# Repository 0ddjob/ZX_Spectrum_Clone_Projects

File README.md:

# ZX Spectrum Clone Projects
Hardware projects & information for Sinclair ZX Spectrum clone computers

## [Datasheets](/Datasheets)
Relevant datasheets for PCB designs.<br>

## [Belarus Byte DIN to VGA](/Belarus_Byte_DIN-to-VGA)
Convert 5-pin DIN video output to DE15 VGA:

- Pin 1 = synch
- Pin 2 = ground
- Pin 3 = blue
- Pin 4 = green
- Pin 5 = red

## [Leningrad-2 DIN to VGA](/Leningrad_2_DIN-to-VGA)
Convert 5-pin DIN video output to DE15 VGA:

- Pin 1 = audio
- Pin 2 = blue
- Pin 3 = red
- Pin 4 = video
- Pin 5 = green
- Sheath = ground

## [Leningrad 2 Expansion](/Leningrad_2_Expansion)
Experimental board to convert the 2x32 (2.5mm pin pitch) expansion header to standard ZX Spectrum edge connector.

## [Moldova BYTE DIN to VGA](/Moldova_BYTE_DIN-to-VGA)
There are two types of BYTE from Moldova: the "Red BYTE" (in a red case with 7-pin DIN) and the "Speccy BYTE" (looks like a Spectrum with a 5-pin DIN).

- Pin 1 = composite video (not connected)
- Pin 2 = composite synch
- Pin 3 = blue
- Pin 4 = green
- Pin 5 = red
- Pin 6 = ground
- Pin 7 = audio

## [Nafanya](/Nafanya)

## [Orel BK DIN to VGA](/Orel_BK_DIN-to-VGA)

## [RGB to VGA](/RGB_to_VGA)

## [Sirius](/Sirius)

## [ZX Spectrum Pioneer 2 Keyboard](/ZX_Spectrum_Pioneer-2_Keyboard)
Work in progress replacement.

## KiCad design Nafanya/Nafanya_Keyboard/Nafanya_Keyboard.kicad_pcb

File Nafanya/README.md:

# Нафаня (Nafanya) ZX Spectrum Clone
The Нафаня is a late Soviet-era (1991) ZX Spectrum clone out of the Russian SFSR.<br>  
My Нафаня is serial no. 00872.<br>

My particular example has a nice, ceramic Z80 from DDR (East Germany) as well as a ceramic БМК (Basic Matrix Crystal, Soviet version of a ULA or Gate Array).<br>

It looked like the original, good quality capacitors were removed from my machine due to their precious-metal content.  They were substituted with poor quality replacements.  I, in turn, replaced them with better quality ones ... this greatly stabilised the RGB video output!  I also added a lot more decoupling capacitors - there was provision for them on the board but they were not installed.<br>

## [Video](https://www.youtube.com/playlist?list=PL5pwokf56wMLiZ0rl97ZL9QdxtgF-uewT)
My YouTube videos:
- [Part 1 (Power On & Troubleshooting)](https://youtu.be/pPQIZv7UhS0)
- [Part 2 (Quick Update)](https://youtu.be/jH4AOVMjng8)
- [Part 3 (Replacement Keyboard Plans)](https://youtu.be/gZ2KwFe9IKs)

## [ROM](/ROM)
The ROM from my machine can be found in this repository.<br>

It has a pretty cool boot screen - I assume this is depicting the character "Нафаня" the computer is named after, a домовой (domovoy, or house spirit) from the Soviet animated film series "Домовёнок Кузя" (Domovyonok Kuzya, or "Kuzya the Little Domovoy") which is based on a children's book by Tatiana Aleksandrova.<br>

## [New Keyboard](/Nafanya_Keyboard)
The keyboard is not terribly good. Here is a re-designed one using tactile switches that should fit in the existing case.<br>

### Status
6-Apr-2025:  Still being finalised. The switch positions are slightly off as you go from left to right.
17-Apr-2025: Finalised switch layout, sent for test fabrication.

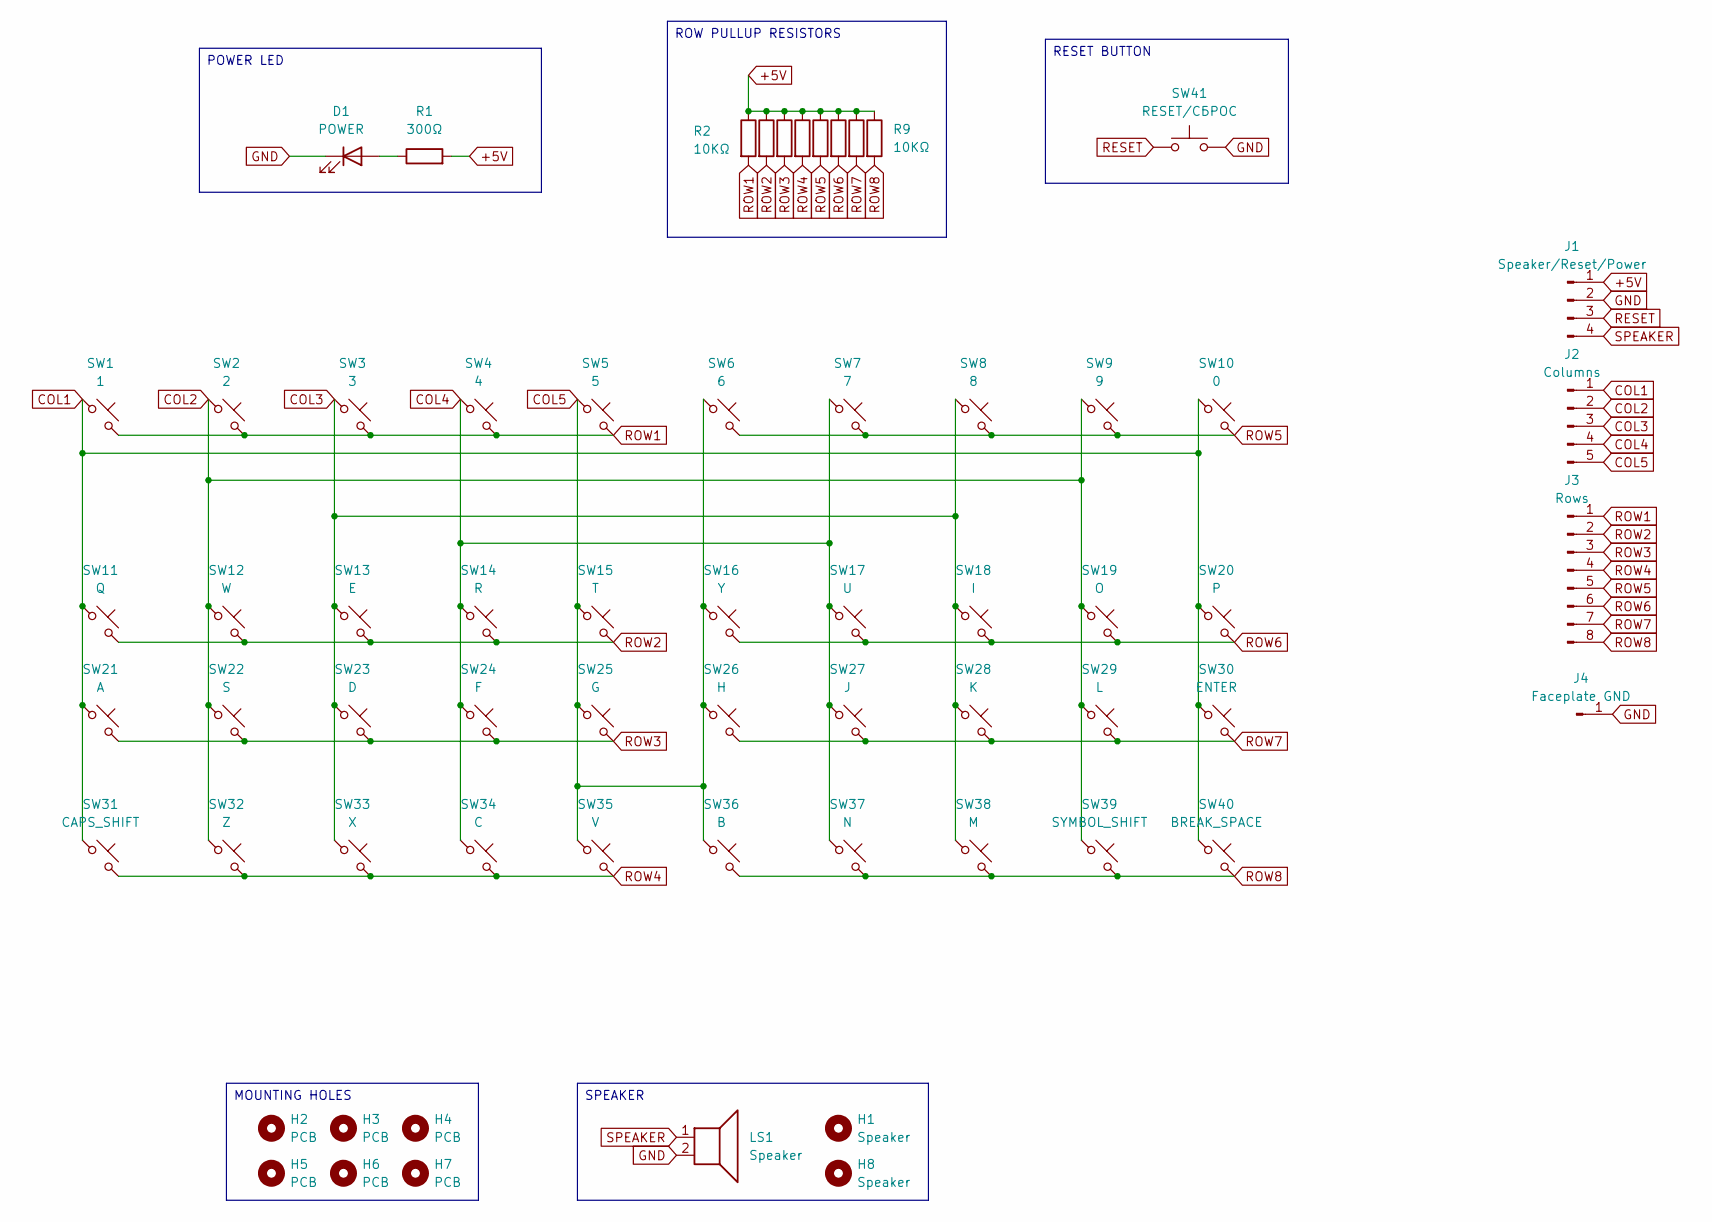
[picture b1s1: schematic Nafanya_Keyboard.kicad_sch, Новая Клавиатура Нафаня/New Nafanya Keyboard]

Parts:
D1: POWER; LED_D5.0mm
H1, H8: Speaker; MountingHole_3.2mm_M3
H2, H3, H4, H5, H6, H7: PCB; MountingHole_3.2mm_M3
J1: Speaker/Reset/Power; PinHeader_1x04_P2.54mm_Horizontal
J2: Columns; PinHeader_1x05_P2.54mm_Horizontal
J3: Rows; PinHeader_1x08_P2.54mm_Horizontal
J4: Faceplate GND; PinSocket_1x01_P2.54mm_Vertical
LS1: Speaker; PinHeader_1x02_P2.54mm_Vertical
R1: 300Ω; R_Axial_DIN0207_L6.3mm_D2.5mm_P7.62mm_Horizontal
R2, R3, R4, R5, R6, R7, R8, R9: 10KΩ; R_Axial_DIN0207_L6.3mm_D2.5mm_P7.62mm_Horizontal
SW1: 1; SW_PUSH_6mm
SW2: 2; SW_PUSH_6mm
SW3: 3; SW_PUSH_6mm
SW4: 4; SW_PUSH_6mm
SW5: 5; SW_PUSH_6mm
SW6: 6; SW_PUSH_6mm
SW7: 7; SW_PUSH_6mm
SW8: 8; SW_PUSH_6mm
SW9: 9; SW_PUSH_6mm
SW10: 0; SW_PUSH_6mm
SW11: Q; SW_PUSH_6mm
SW12: W; SW_PUSH_6mm
SW13: E; SW_PUSH_6mm
SW14: R; SW_PUSH_6mm
SW15: T; SW_PUSH_6mm
SW16: Y; SW_PUSH_6mm
SW17: U; SW_PUSH_6mm
SW18: I; SW_PUSH_6mm
SW19: O; SW_PUSH_6mm
SW20: P; SW_PUSH_6mm
SW21: A; SW_PUSH_6mm
SW22: S; SW_PUSH_6mm
SW23: D; SW_PUSH_6mm
SW24: F; SW_PUSH_6mm
SW25: G; SW_PUSH_6mm
SW26: H; SW_PUSH_6mm
SW27: J; SW_PUSH_6mm
SW28: K; SW_PUSH_6mm
SW29: L; SW_PUSH_6mm
SW30: ENTER; SW_PUSH_6mm
SW31: CAPS_SHIFT; SW_PUSH_6mm
SW32: Z; SW_PUSH_6mm
SW33: X; SW_PUSH_6mm
SW34: C; SW_PUSH_6mm
SW35: V; SW_PUSH_6mm
SW36: B; SW_PUSH_6mm
SW37: N; SW_PUSH_6mm
SW38: M; SW_PUSH_6mm
SW39: SYMBOL_SHIFT; SW_PUSH_6mm
SW40: BREAK_SPACE; SW_PUSH_6mm
SW41: RESET/СБРОС; SW_PUSH_6mm

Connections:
+5V: J1.1, R1.2, R2.1, R3.1, R4.1, R5.1, R6.1, R7.1, R8.1, R9.1
COL1: J2.1, SW1.1, SW10.1, SW11.1, SW20.1, SW21.1, SW30.1, SW31.1, SW40.1
COL2: J2.2, SW2.1, SW9.1, SW12.1, SW19.1, SW22.1, SW29.1, SW32.1, SW39.1
COL3: J2.3, SW3.1, SW8.1, SW13.1, SW18.1, SW23.1, SW28.1, SW33.1, SW38.1
COL4: J2.4, SW4.1, SW7.1, SW14.1, SW17.1, SW24.1, SW27.1, SW34.1, SW37.1
COL5: J2.5, SW5.1, SW6.1, SW15.1, SW16.1, SW25.1, SW26.1, SW35.1, SW36.1
GND: D1.1 (K), J1.2, J4.1, LS1.2, SW41.2
unnamed: D1.2 (A), R1.1
RESET: J1.3, SW41.1
ROW1: J3.1, R2.2, SW1.2, SW2.2, SW3.2, SW4.2, SW5.2
ROW2: J3.2, R3.2, SW11.2, SW12.2, SW13.2, SW14.2, SW15.2
ROW3: J3.3, R4.2, SW21.2, SW22.2, SW23.2, SW24.2, SW25.2
ROW4: J3.4, R5.2, SW31.2, SW32.2, SW33.2, SW34.2, SW35.2
ROW5: J3.5, R6.2, SW6.2, SW7.2, SW8.2, SW9.2, SW10.2
ROW6: J3.6, R7.2, SW16.2, SW17.2, SW18.2, SW19.2, SW20.2
ROW7: J3.7, R8.2, SW26.2, SW27.2, SW28.2, SW29.2, SW30.2
ROW8: J3.8, R9.2, SW36.2, SW37.2, SW38.2, SW39.2, SW40.2
SPEAKER: J1.4, LS1.1

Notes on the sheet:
RESET BUTTON
MOUNTING HOLES
POWER LED
SPEAKER
ROW PULLUP RESISTORS

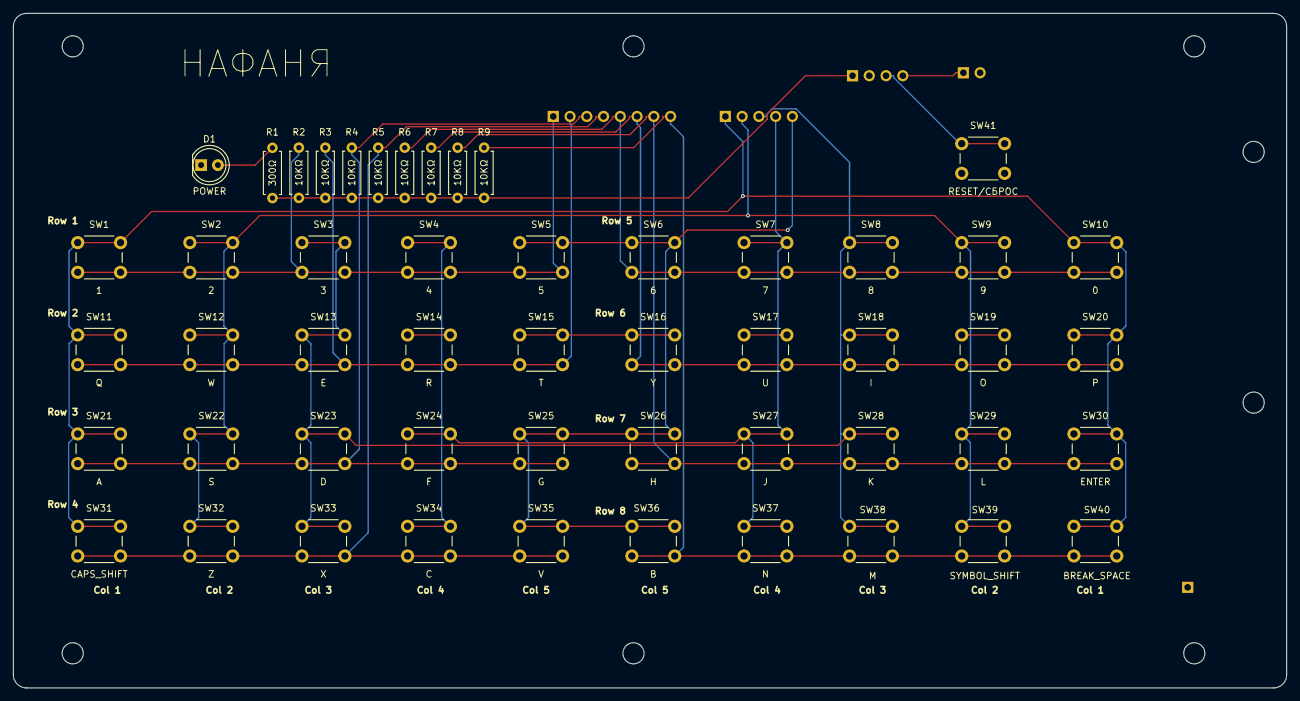
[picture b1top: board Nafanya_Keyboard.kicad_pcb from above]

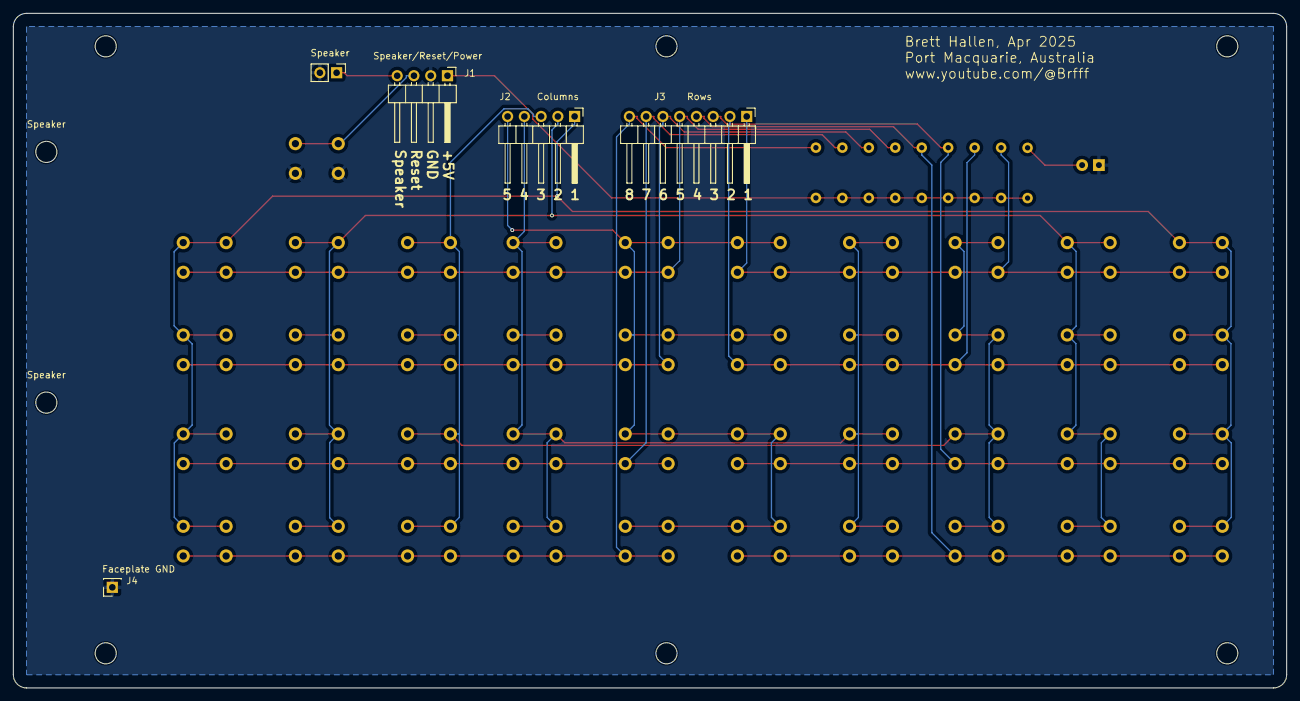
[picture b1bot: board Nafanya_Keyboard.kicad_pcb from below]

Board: 2 copper layers, 193.0 x 102.2 mm, 64 parts (7 on the bottom side), 18 nets.

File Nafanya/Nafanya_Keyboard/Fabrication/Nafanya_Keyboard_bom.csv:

Designator,Quantity,Value,Footprint,Package,MPN,DNP,Mount_Type,Description,Sim.Pins
D1,1,POWER,LED_D5.0mm,,,,tht,Light emitting diode,1=K 2=A
J1,1,Speaker/Reset/Power,PinHeader_1x04_P2.54mm_Horizontal,,,,tht,"Generic connector, single row, 01x04, script generated",
J2,1,Columns,PinHeader_1x05_P2.54mm_Horizontal,,,,tht,"Generic connector, single row, 01x05, script generated",
J3,1,Rows,PinHeader_1x08_P2.54mm_Horizontal,,,,tht,"Generic connector, single row, 01x08, script generated",
J4,1,Faceplate GND,PinSocket_1x01_P2.54mm_Vertical,,,,tht,"Generic connector, single row, 01x01, script generated",
LS1,1,Speaker,PinHeader_1x02_P2.54mm_Vertical,,,,tht,Speaker,
R1,1,300Ω,R_Axial_DIN0207_L6.3mm_D2.5mm_P7.62mm_Horizontal,,,,tht,Resistor,
"R2, R3, R4, R5, R6, R7, R8, R9",8,10KΩ,R_Axial_DIN0207_L6.3mm_D2.5mm_P7.62mm_Horizontal,,,,tht,Resistor,
SW1,1,1,SW_PUSH_6mm_H8.5mm,,,,tht,"Push button switch, normally open, two pins, 45° tilted",
SW10,1,0,SW_PUSH_6mm_H8.5mm,,,,tht,"Push button switch, normally open, two pins, 45° tilted",
SW11,1,Q,SW_PUSH_6mm_H8.5mm,,,,tht,"Push button switch, normally open, two pins, 45° tilted",
SW12,1,W,SW_PUSH_6mm_H8.5mm,,,,tht,"Push button switch, normally open, two pins, 45° tilted",
SW13,1,E,SW_PUSH_6mm_H8.5mm,,,,tht,"Push button switch, normally open, two pins, 45° tilted",
SW14,1,R,SW_PUSH_6mm_H8.5mm,,,,tht,"Push button switch, normally open, two pins, 45° tilted",
SW15,1,T,SW_PUSH_6mm_H8.5mm,,,,tht,"Push button switch, normally open, two pins, 45° tilted",
SW16,1,Y,SW_PUSH_6mm_H8.5mm,,,,tht,"Push button switch, normally open, two pins, 45° tilted",
SW17,1,U,SW_PUSH_6mm_H8.5mm,,,,tht,"Push button switch, normally open, two pins, 45° tilted",
SW18,1,I,SW_PUSH_6mm_H8.5mm,,,,tht,"Push button switch, normally open, two pins, 45° tilted",
SW19,1,O,SW_PUSH_6mm_H8.5mm,,,,tht,"Push button switch, normally open, two pins, 45° tilted",
SW2,1,2,SW_PUSH_6mm_H8.5mm,,,,tht,"Push button switch, normally open, two pins, 45° tilted",
SW20,1,P,SW_PUSH_6mm_H8.5mm,,,,tht,"Push button switch, normally open, two pins, 45° tilted",
SW21,1,A,SW_PUSH_6mm_H8.5mm,,,,tht,"Push button switch, normally open, two pins, 45° tilted",
SW22,1,S,SW_PUSH_6mm_H8.5mm,,,,tht,"Push button switch, normally open, two pins, 45° tilted",
SW23,1,D,SW_PUSH_6mm_H8.5mm,,,,tht,"Push button switch, normally open, two pins, 45° tilted",
SW24,1,F,SW_PUSH_6mm_H8.5mm,,,,tht,"Push button switch, normally open, two pins, 45° tilted",
SW25,1,G,SW_PUSH_6mm_H8.5mm,,,,tht,"Push button switch, normally open, two pins, 45° tilted",
SW26,1,H,SW_PUSH_6mm_H8.5mm,,,,tht,"Push button switch, normally open, two pins, 45° tilted",
SW27,1,J,SW_PUSH_6mm_H8.5mm,,,,tht,"Push button switch, normally open, two pins, 45° tilted",
SW28,1,K,SW_PUSH_6mm_H8.5mm,,,,tht,"Push button switch, normally open, two pins, 45° tilted",
SW29,1,L,SW_PUSH_6mm_H8.5mm,,,,tht,"Push button switch, normally open, two pins, 45° tilted",
SW3,1,3,SW_PUSH_6mm_H8.5mm,,,,tht,"Push button switch, normally open, two pins, 45° tilted",
SW30,1,ENTER,SW_PUSH_6mm_H8.5mm,,,,tht,"Push button switch, normally open, two pins, 45° tilted",
SW31,1,CAPS_SHIFT,SW_PUSH_6mm_H8.5mm,,,,tht,"Push button switch, normally open, two pins, 45° tilted",
SW32,1,Z,SW_PUSH_6mm_H8.5mm,,,,tht,"Push button switch, normally open, two pins, 45° tilted",
SW33,1,X,SW_PUSH_6mm_H8.5mm,,,,tht,"Push button switch, normally open, two pins, 45° tilted",
SW34,1,C,SW_PUSH_6mm_H8.5mm,,,,tht,"Push button switch, normally open, two pins, 45° tilted",
SW35,1,V,SW_PUSH_6mm_H8.5mm,,,,tht,"Push button switch, normally open, two pins, 45° tilted",
SW36,1,B,SW_PUSH_6mm_H8.5mm,,,,tht,"Push button switch, normally open, two pins, 45° tilted",
SW37,1,N,SW_PUSH_6mm_H8.5mm,,,,tht,"Push button switch, normally open, two pins, 45° tilted",
SW38,1,M,SW_PUSH_6mm_H8.5mm,,,,tht,"Push button switch, normally open, two pins, 45° tilted",
SW39,1,SYMBOL_SHIFT,SW_PUSH_6mm_H8.5mm,,,,tht,"Push button switch, normally open, two pins, 45° tilted",
SW4,1,4,SW_PUSH_6mm_H8.5mm,,,,tht,"Push button switch, normally open, two pins, 45° tilted",
SW40,1,BREAK_SPACE,SW_PUSH_6mm_H8.5mm,,,,tht,"Push button switch, normally open, two pins, 45° tilted",
SW41,1,RESET/СБРОС,SW_PUSH_6mm_H8.5mm,,,,tht,"Push button switch, generic, two pins",
SW5,1,5,SW_PUSH_6mm_H8.5mm,,,,tht,"Push button switch, normally open, two pins, 45° tilted",
SW6,1,6,SW_PUSH_6mm_H8.5mm,,,,tht,"Push button switch, normally open, two pins, 45° tilted",
SW7,1,7,SW_PUSH_6mm_H8.5mm,,,,tht,"Push button switch, normally open, two pins, 45° tilted",
SW8,1,8,SW_PUSH_6mm_H8.5mm,,,,tht,"Push button switch, normally open, two pins, 45° tilted",
SW9,1,9,SW_PUSH_6mm_H8.5mm,,,,tht,"Push button switch, normally open, two pins, 45° tilted",

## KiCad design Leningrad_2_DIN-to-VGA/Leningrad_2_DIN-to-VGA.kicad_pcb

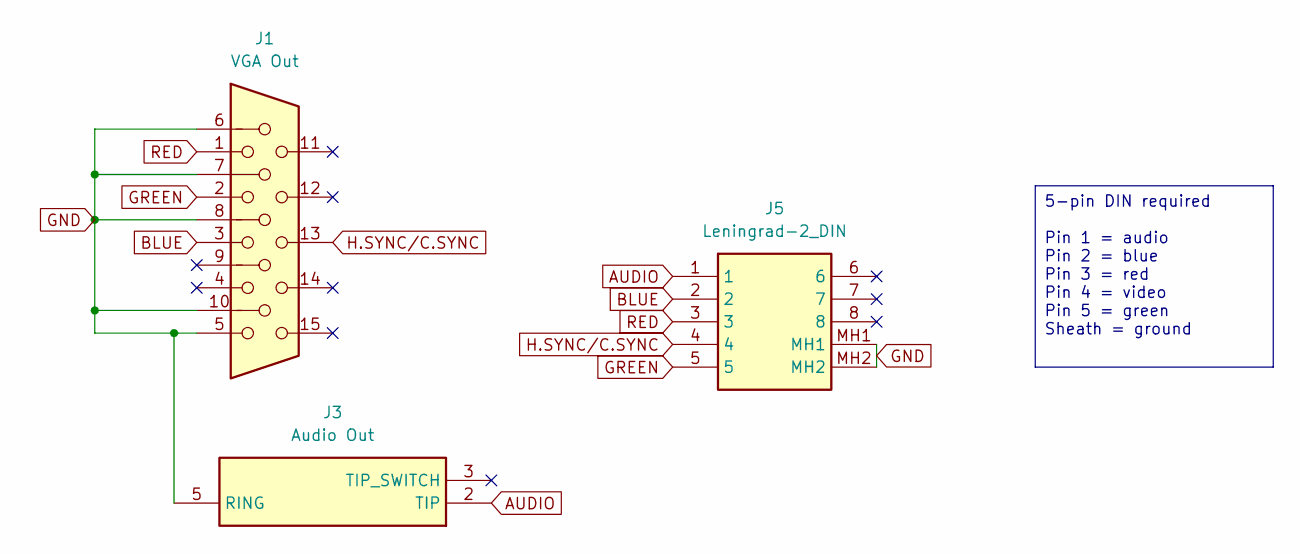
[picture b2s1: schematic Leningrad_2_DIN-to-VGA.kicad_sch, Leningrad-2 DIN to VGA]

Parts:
J1: VGA Out; DSUB-15-HD_Socket_Horizontal_P2.29x2.54mm_EdgePinOffset8.35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
J3: Audio Out; SJ3350820BTR; Mouser Part Number 179-SJ3-350820B-TR
J5: Leningrad-2_DIN; 6710801; Manufacturer_Part_Number 671-0801

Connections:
AUDIO: J3.2 (TIP), J5.1
BLUE: J1.3, J5.2
GND: J1.5, J1.6, J1.7, J1.8, J1.10, J3.5 (RING), J5.MH1, J5.MH2
GREEN: J1.2, J5.5
H.SYNC/C.SYNC: J1.13, J5.4
RED: J1.1, J5.3

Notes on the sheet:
5-pin DIN required Pin 1 = audio Pin 2 = blue Pin 3 = red Pin 4 = video Pin 5 = green Sheath = ground

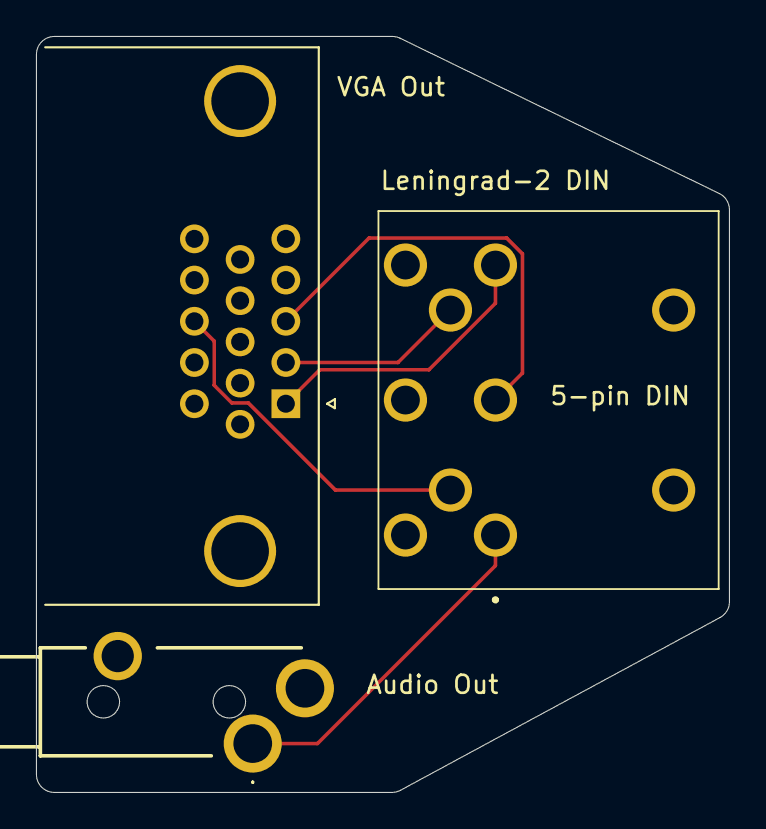
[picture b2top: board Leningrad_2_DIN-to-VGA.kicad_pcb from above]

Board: 2 copper layers, 38.5 x 42.0 mm, 3 parts (0 on the bottom side), 6 nets.

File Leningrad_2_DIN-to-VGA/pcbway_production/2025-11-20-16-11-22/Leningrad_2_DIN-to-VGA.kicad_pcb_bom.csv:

Designator,Quantity,Value,Footprint,Package,MPN,DNP,Mount_Type,Description,Height,Mouser Part Number,Mouser Price/Stock,Manufacturer_Name
J1,1,VGA Out,DSUB-15-HD_Socket_Horizontal_P2.29x2.54mm_EdgePinOffset8.35mm_Housed_MountingHolesOffset10.89mm,,,,tht,"15-pin D-SUB connector, socket (female), High density (3 columns), Triple Row, Generic, VGA-connector",,,,
J3,1,Audio Out,SJ3350820BTR,,SJ3-350820B-TR,,tht,"3.5 mm Stereo Jack, Through Hole, 2 Conductors, 1 Internal Switches,  Tape & Reel Packaging",5.3,179-SJ3-350820B-TR,https://www.mouser.co.uk/ProductDetail/Same-Sky/SJ3-350820B-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,Same Sky
J5,1,Leningrad-2_DIN,6710801,,671-0801,,tht,"Deltron 8 Pole Right Angle Din Socket Socket, 2A, 100 V ac, Lockable",19.5,,,DELTRON COMPONENTS

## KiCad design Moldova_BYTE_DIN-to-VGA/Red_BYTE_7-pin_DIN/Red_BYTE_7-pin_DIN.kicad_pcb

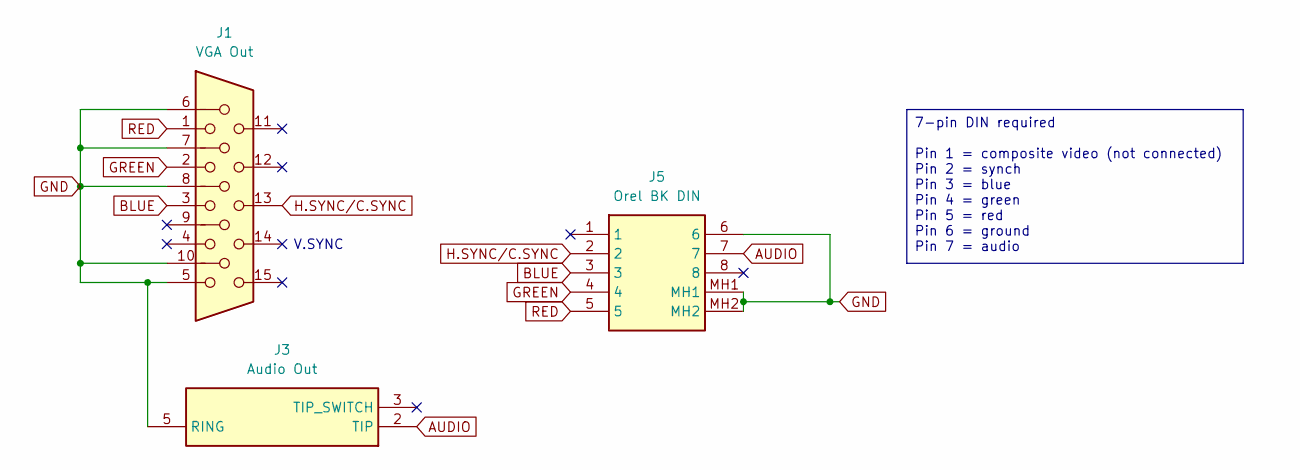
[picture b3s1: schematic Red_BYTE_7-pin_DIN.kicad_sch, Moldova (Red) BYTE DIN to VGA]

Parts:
J1: VGA Out; DSUB-15-HD_Socket_Horizontal_P2.29x2.54mm_EdgePinOffset8.35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
J3: Audio Out; SJ3350820BTR; Mouser Part Number 179-SJ3-350820B-TR
J5: Orel BK DIN; 6710801; Manufacturer_Part_Number 671-0801

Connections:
AUDIO: J3.2 (TIP), J5.7
BLUE: J1.3, J5.3
GND: J1.5, J1.6, J1.7, J1.8, J1.10, J3.5 (RING), J5.6, J5.MH1, J5.MH2
GREEN: J1.2, J5.4
H.SYNC/C.SYNC: J1.13, J5.2
RED: J1.1, J5.5

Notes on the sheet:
V.SYNC
7-pin DIN required Pin 1 = composite video (not connected) Pin 2 = synch Pin 3 = blue Pin 4 = green Pin 5 = red Pin 6 = ground Pin 7 = audio

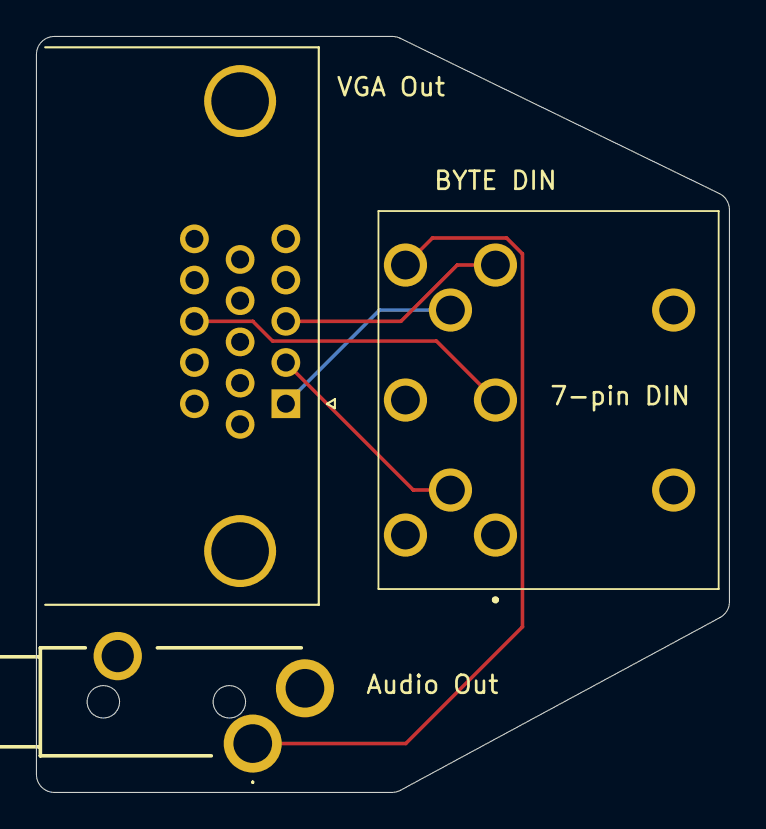
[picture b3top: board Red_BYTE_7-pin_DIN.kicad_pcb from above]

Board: 2 copper layers, 38.5 x 42.0 mm, 3 parts (0 on the bottom side), 6 nets.

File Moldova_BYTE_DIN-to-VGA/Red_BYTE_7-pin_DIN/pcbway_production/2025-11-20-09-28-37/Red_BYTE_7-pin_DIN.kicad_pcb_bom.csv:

Designator,Quantity,Value,Footprint,Package,MPN,DNP,Mount_Type,Description,Height,Mouser Part Number,Mouser Price/Stock,Manufacturer_Name
J1,1,VGA Out,DSUB-15-HD_Socket_Horizontal_P2.29x2.54mm_EdgePinOffset8.35mm_Housed_MountingHolesOffset10.89mm,,,,tht,"15-pin D-SUB connector, socket (female), High density (3 columns), Triple Row, Generic, VGA-connector",,,,
J3,1,Audio Out,SJ3350820BTR,,SJ3-350820B-TR,,tht,"3.5 mm Stereo Jack, Through Hole, 2 Conductors, 1 Internal Switches,  Tape & Reel Packaging",5.3,179-SJ3-350820B-TR,https://www.mouser.co.uk/ProductDetail/Same-Sky/SJ3-350820B-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,Same Sky
J5,1,Orel BK DIN,6710801,,671-0801,,tht,"Deltron 8 Pole Right Angle Din Socket Socket, 2A, 100 V ac, Lockable",19.5,,,DELTRON COMPONENTS

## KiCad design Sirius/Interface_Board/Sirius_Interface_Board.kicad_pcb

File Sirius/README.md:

# Сириус (Sirius) Sinclair ZX Spectrum Clone
## Introduction
I have two examples of this machine - they have the same case & keyboard but the motherboard is different.  I'm mainly interested in the smaller board as this seems to be the smallest implementation of a ZX Spectrum I've come across.

This machine was initially a bit of a mystery - well, obviously it's a Sinclair ZX Spectrum clone.  It has all Soviet-era parts (dated mostly 1991 & 1992) including a beautiful, ceramic Т34ВМ1 CPU, a Т34РЕ1-020 ROM (containing the Czechoslovak "Didaktik Skalica" firmware) and absolutely no manufacture markings on the case or motherboard.

Thanks to some sleuthing by Martin (via Patreon) who discovered that the machine (case at least) appears to be a "Sirius" from Russia (confirmed also with UCHC, Ukrainian Computing History Community, on Telegram):
https://sblive.narod.ru/ZX-Spectrum/Sirius/Sirius.htm

Thanks to Eugene on UCHC for his insight:
"Actually, this is one of numerous cheap clones that built around latest Soviet ULA replacement. This one, in particular, created by small garage company with a quite shitty soldering and assembling.  And board itself seems to be assembled somewhere using automated production line, so seems they have ordered boards somewhere else and then assemble them in case. This can explain why boards in these instances are different."

It was initially AC powered with a very simple and unsafe looking transformer (assuming 220VAC-to-9VAC), a КЦ410Б bridge rectifier and a КРЕН5А 5V linear regulator.  I will replace these with a simple 2.1mm DC socket for direct 5VDC input (i.e. USB charger).  On booting it was drawing about 330mA at 5V.

It utilises a Soviet equivalent to a Gate Array or ULA called a БМК (Базового Матричного Кристалла, or Basic Matrix Crystal) ... the КА1515ХМ1-216.  I have had very little success with machines that use this chip actually working ... however it does greatly simplify the circuit design!

The only other major chips are the Т34ВМ1 Soviet Z80 clone, later called the КР1858ВМ1 or КМ1858ВМ1 depending on case type), a Т34РЕ1 (Spectrum ROM), 64KBytes of DRAM using КР565РУ5 and a few other support chips.

The machine only has three ports: 5-pin DIN for joystick, 5-pin DIN for RGBS video & sound output and a 3-pin DIN for cassette input/output.  It also has a reset button.

## Videos
- [Сириус (Sirius) ZX Spectrum Clone: Part 1 (First Look & Power On)](https://youtu.be/TphnZRfjiL4)
- [Сириус (Sirius) ZX Spectrum Clone: Part 2 (RGB & Tape In)](https://youtu.be/R5iWXHqjOgQ)
- [Сириус (Sirius) ZX Spectrum Clone: Part 3 (Smallest Speccy board?)](https://youtu.be/3xgzQrBvwQw)

## [Original Information](/Original_Documentation)
Original schematic & board layout details from [here](https://sblive.narod.ru/ZX-Spectrum/Sirius/Sirius.htm).

## [Updated Schematic](/New_Schematic)
I'm working on creating a cleaner version of the schematic.  I originally wanted to use it as a basis for a new design using the БМК but there is already a modern design available [[LUT216]](https://sblive.narod.ru/ZX-Spectrum/LUT216/LUT216.htm) that looks quite interesting.

### Status
15-Jun-2025: Updated KiCad schematic is work-in-progress<br>

## [Interface Board](/Interface_Board)
Such a beautiful little board deserves to be seen and not hidden away in some ho-hum case.  I'm planning to mount my Sirius board on a Perspex place with a membrane keyboard.  Thus I need a separate board with all the interfaces on it, hence this design.

### Status
16-Jun-2025: Submitted to PCBWAY for test fabrication<br>

## [Images](/Images)
Pictures of my machine.

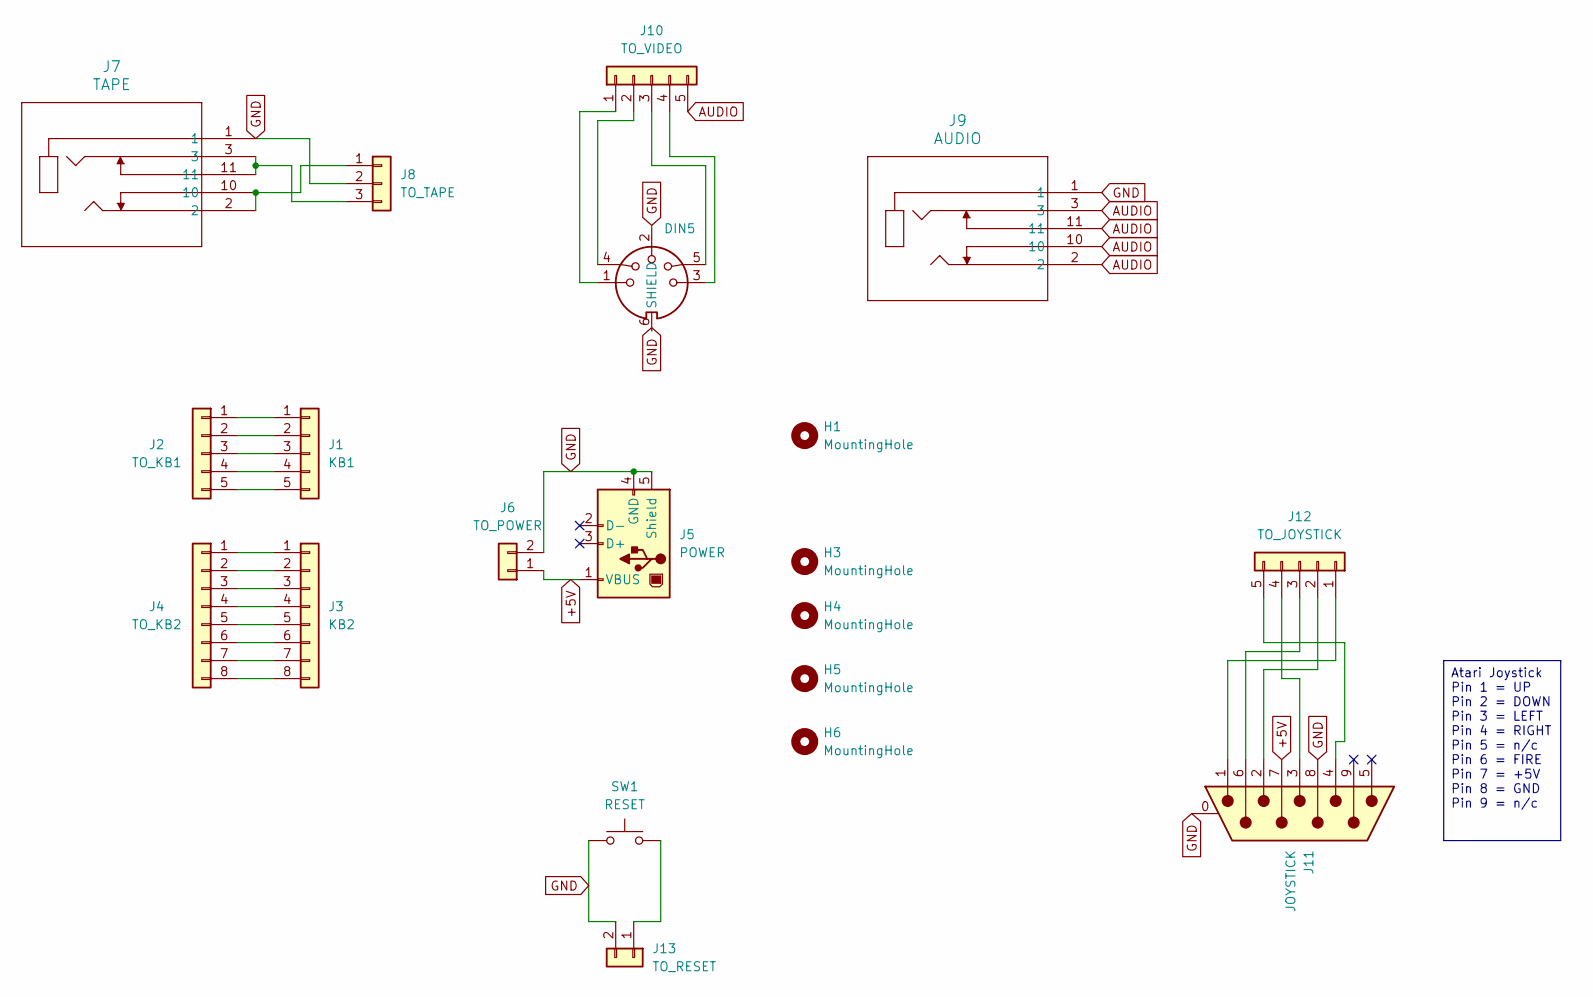
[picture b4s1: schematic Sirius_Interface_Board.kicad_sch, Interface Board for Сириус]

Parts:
H1, H3, H4, H5, H6: MountingHole; MountingHole_3.2mm_M3
J1: KB1; PinHeader_1x05_P2.54mm_Vertical
J2: TO_KB1; PinHeader_1x05_P2.54mm_Vertical
J3: KB2; PinHeader_1x08_P2.54mm_Vertical
J4: TO_KB2; PinHeader_1x08_P2.54mm_Vertical
J5: POWER; USB_B_Lumberg_2411_02_Horizontal
J6: TO_POWER; PinHeader_1x02_P2.54mm_Vertical
J7: TAPE; 35RAPC4BHN2_SWC
J8: TO_TAPE; PinHeader_1x03_P2.54mm_Vertical
J9: AUDIO; 35RAPC4BHN2_SWC
J10: TO_VIDEO; PinHeader_1x05_P2.54mm_Vertical
J11: JOYSTICK; DSUB-9_Pins_Horizontal_P2.77x2.84mm_EdgePinOffset7.70mm_Hou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
J12: TO_JOYSTICK; PinHeader_1x05_P2.54mm_Vertical
J13: TO_RESET; PinHeader_1x02_P2.54mm_Vertical
J15: DIN5; DIN5_MIDI
SW1: RESET; Switch_Tactile_6mm

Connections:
+5V: J5.1 (VBUS), J6.1, J11.7
AUDIO: J9.2, J9.3, J9.10, J9.11, J10.5
GND: J5.4 (GND), J5.5 (Shield), J6.2, J7.1, J8.2, J9.1, J11.0 (PAD), J11.8, J13.2, J15.2, J15.6 (SHIELD), SW1.1
unnamed: J1.1, J2.1
unnamed: J1.2, J2.2
unnamed: J1.3, J2.3
unnamed: J1.4, J2.4
unnamed: J1.5, J2.5
unnamed: J3.1, J4.1
unnamed: J3.2, J4.2
unnamed: J3.3, J4.3
unnamed: J3.4, J4.4
unnamed: J3.5, J4.5
unnamed: J3.6, J4.6
unnamed: J3.7, J4.7
unnamed: J3.8, J4.8
unnamed: J7.2, J7.10, J8.1
unnamed: J7.3, J7.11, J8.3
unnamed: J10.1, J15.1
unnamed: J10.2, J15.4
unnamed: J10.3, J15.5
unnamed: J10.4, J15.3
unnamed: J11.1, J12.1
unnamed: J11.2, J12.2
unnamed: J11.6, J12.3
unnamed: J11.3, J12.4
unnamed: J11.4, J12.5
unnamed: J13.1, SW1.2

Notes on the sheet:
Atari Joystick Pin 1 = UP Pin 2 = DOWN Pin 3 = LEFT Pin 4 = RIGHT Pin 5 = n/c Pin 6 = FIRE Pin 7 = +5V Pin 8 = GND Pin 9 = n/c

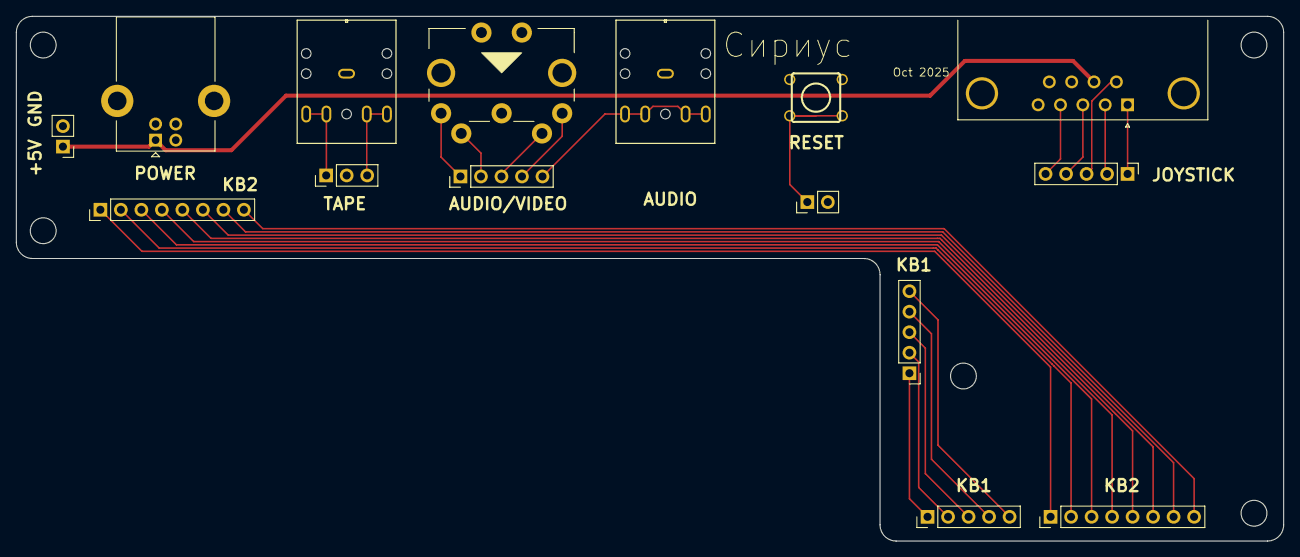
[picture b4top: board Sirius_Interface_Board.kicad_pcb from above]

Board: 2 copper layers, 157.0 x 65.0 mm, 20 parts (0 on the bottom side), 28 nets.

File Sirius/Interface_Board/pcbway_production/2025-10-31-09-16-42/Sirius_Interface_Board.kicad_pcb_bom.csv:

Designator,Quantity,Value,Footprint,Package,MPN,DNP,Mount_Type,Description
J1,1,KB1,PinHeader_1x05_P2.54mm_Vertical,,,,tht,"Generic connector, single row, 01x05, script generated (kicad-library-utils/schlib/autogen/connector/)"
J10,1,TO_VIDEO,PinHeader_1x05_P2.54mm_Vertical,,,,tht,"Generic connector, single row, 01x05, script generated (kicad-library-utils/schlib/autogen/connector/)"
J11,1,JOYSTICK,DSUB-9_Pins_Horizontal_P2.77x2.84mm_EdgePinOffset7.70mm_Housed_MountingHolesOffset9.12mm,,,,tht,"9-pin D-SUB connector, pins (male), Mounting Hole"
J12,1,TO_JOYSTICK,PinHeader_1x05_P2.54mm_Vertical,,,,tht,"Generic connector, single row, 01x05, script generated (kicad-library-utils/schlib/autogen/connector/)"
J13,1,TO_RESET,PinHeader_1x02_P2.54mm_Vertical,,,,tht,"Generic connector, single row, 01x02, script generated (kicad-library-utils/schlib/autogen/connector/)"
J15,1,DIN5,DIN5_MIDI,,,,tht,
J2,1,TO_KB1,PinHeader_1x05_P2.54mm_Vertical,,,,tht,"Generic connector, single row, 01x05, script generated (kicad-library-utils/schlib/autogen/connector/)"
J3,1,KB2,PinHeader_1x08_P2.54mm_Vertical,,,,tht,"Generic connector, single row, 01x08, script generated (kicad-library-utils/schlib/autogen/connector/)"
J4,1,TO_KB2,PinHeader_1x08_P2.54mm_Vertical,,,,tht,"Generic connector, single row, 01x08, script generated (kicad-library-utils/schlib/autogen/connector/)"
J5,1,POWER,USB_B_Lumberg_2411_02_Horizontal,,,,tht,USB Type B connector
J6,1,TO_POWER,PinHeader_1x02_P2.54mm_Vertical,,,,tht,"Generic connector, single row, 01x02, script generated (kicad-library-utils/schlib/autogen/connector/)"
J7,1,TAPE,35RAPC4BHN2_SWC,,,,tht,
J8,1,TO_TAPE,PinHeader_1x03_P2.54mm_Vertical,,,,tht,"Generic connector, single row, 01x03, script generated (kicad-library-utils/schlib/autogen/connector/)"
J9,1,AUDIO,35RAPC4BHN2_SWC,,,,tht,
SW1,1,RESET,Switch_Tactile_6mm,,,,tht,"Push button switch, generic, two pins"

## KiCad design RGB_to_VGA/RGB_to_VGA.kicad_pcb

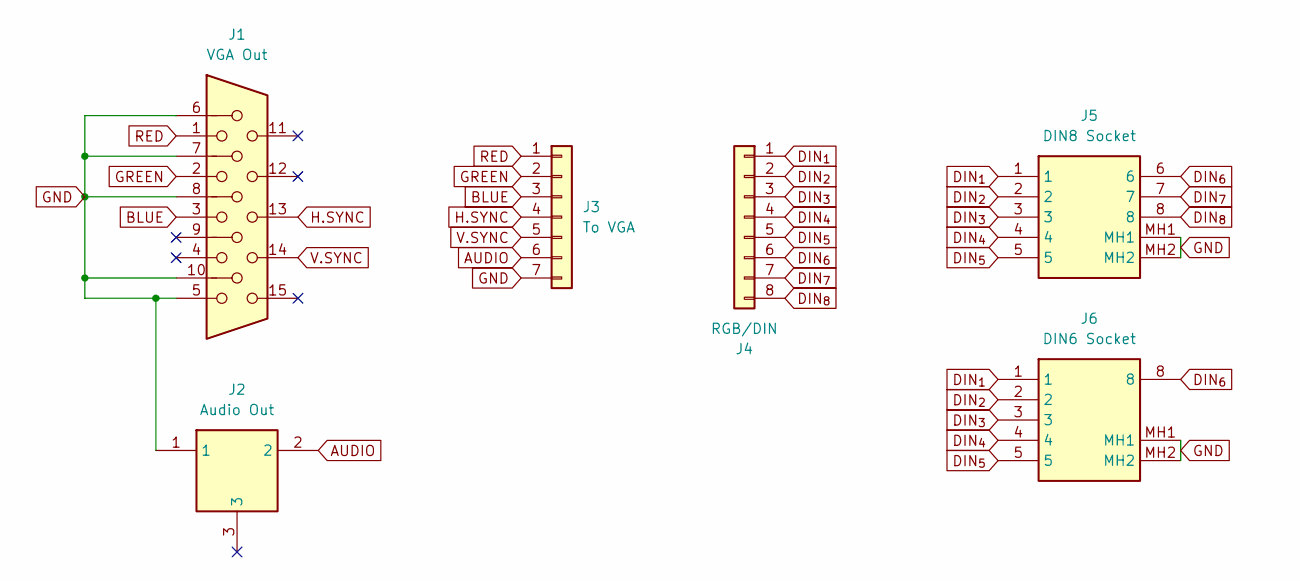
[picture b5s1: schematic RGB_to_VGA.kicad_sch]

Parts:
J1: VGA Out; DSUB-15-HD_Socket_Horizontal_P2.29x2.54mm_EdgePinOffset8.35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
J2: Audio Out; MJ3536N; Mouser Part Number 490-MJ-3536N
J3: To VGA; PinHeader_1x07_P2.54mm_Vertical
J4: RGB/DIN; PinHeader_1x08_P2.54mm_Vertical
J5: DIN8 Socket; 6710801; Manufacturer_Part_Number 671-0801
J6: DIN6 Socket; 6710601; Manufacturer_Part_Number 671-0601

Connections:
AUDIO: J2.2, J3.6
BLUE: J1.3, J3.3
DIN_{1}: J4.1, J5.1, J6.1
DIN_{2}: J4.2, J5.2, J6.2
DIN_{3}: J4.3, J5.3, J6.3
DIN_{4}: J4.4, J5.4, J6.4
DIN_{5}: J4.5, J5.5, J6.5
DIN_{6}: J4.6, J5.6, J6.8
DIN_{7}: J4.7, J5.7
DIN_{8}: J4.8, J5.8
GND: J1.5, J1.6, J1.7, J1.8, J1.10, J2.1, J3.7, J5.MH1, J5.MH2, J6.MH1, J6.MH2
GREEN: J1.2, J3.2
H.SYNC: J1.13, J3.4
RED: J1.1, J3.1
V.SYNC: J1.14, J3.5

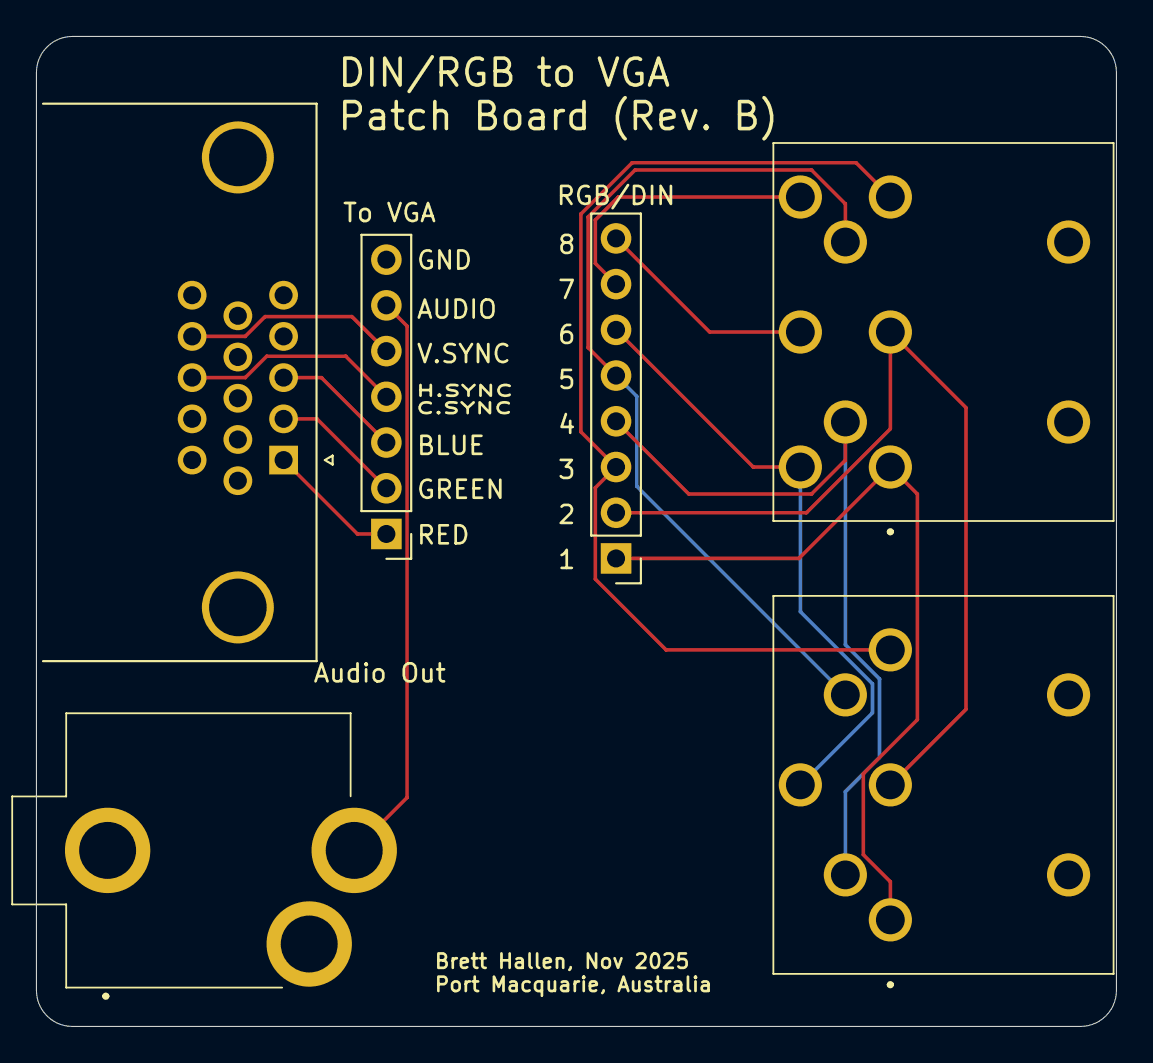
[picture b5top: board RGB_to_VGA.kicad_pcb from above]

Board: 2 copper layers, 60.0 x 55.0 mm, 6 parts (0 on the bottom side), 15 nets.

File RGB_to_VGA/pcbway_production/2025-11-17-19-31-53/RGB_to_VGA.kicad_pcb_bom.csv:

Designator,Quantity,Value,Footprint,Package,MPN,DNP,Mount_Type,Description,Height,Mouser Part Number,Mouser Price/Stock,Manufacturer_Name
J1,1,VGA Out,DSUB-15-HD_Socket_Horizontal_P2.29x2.54mm_EdgePinOffset8.35mm_Housed_MountingHolesOffset10.89mm,,,,tht,"15-pin D-SUB connector, socket (female), High density (3 columns), Triple Row, Generic, VGA-connector",,,,
J2,1,Audio Out,MJ3536N,,MJ-3536N,,tht,"3.5 mm, Mono, Right Angle, Through Hole, 2 Conductors, 1 Internal Switch, Audio Jack Connector",10,490-MJ-3536N,https://www.mouser.co.uk/ProductDetail/Same-Sky/MJ-3536N?qs=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,Same Sky
J3,1,To VGA,PinHeader_1x07_P2.54mm_Vertical,,,,tht,"Generic connector, single row, 01x07, script generated (kicad-library-utils/schlib/autogen/connector/)",,,,
J4,1,RGB/DIN,PinHeader_1x08_P2.54mm_Vertical,,,,tht,"Generic connector, single row, 01x08, script generated (kicad-library-utils/schlib/autogen/connector/)",,,,
J5,1,DIN8 Socket,6710801,,671-0801,,tht,"Deltron 8 Pole Right Angle Din Socket Socket, 2A, 100 V ac, Lockable",19.5,,,DELTRON COMPONENTS
J6,1,DIN6 Socket,6710601,,671-0601,,tht,"Deltron 6 Pole Right Angle Din Socket Socket, 2A, 100 V ac, Lockable",19.5,,,DELTRON COMPONENTS
